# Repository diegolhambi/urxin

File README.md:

# Urxin

A keyboard made inspired by [Urchin](https://github.com/duckyb/urchin), [TOTEM](https://github.com/GEIGEIGEIST/TOTEM) and [Ergonaut One](https://github.com/ergonautkb/one).

## Firmware

A ZMK Module containing the shield can be found in [zmk-keyboard-urxin](https://github.com/diegolhambi/zmk-keyboard-urxin) and an example of implementation can be seen in [zmk-config-urxin](https://github.com/diegolhambi/zmk-config-urxin).

## BOM
List of parts for both sides.

| Name                          | Qty |
|-------------------------------|:---:|
| Kailh PG1350 Hot Swap Sockets |  34 |
| SOD-123 Diodes                |  34 |
| Seeeduino XIAO nRF52840       |  2  |
| Li-Po 601230 battery          |  2  |
| MSK-12C02 SPDT Switch         |  2  |

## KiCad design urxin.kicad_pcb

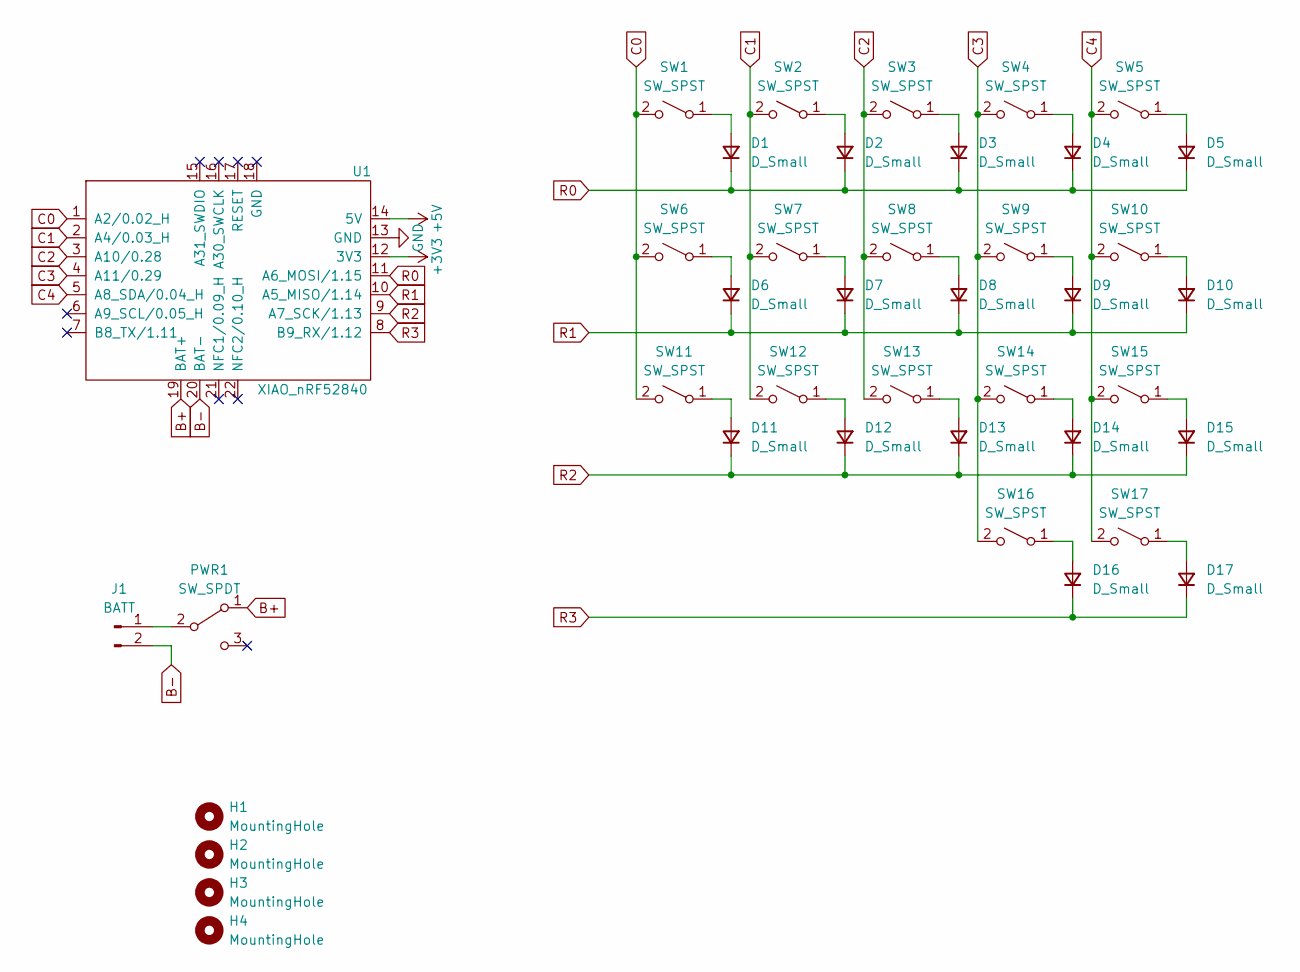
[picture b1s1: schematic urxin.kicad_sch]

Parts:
D1, D2, D3, D4, D5, D6, D7, D8, D9, D10, D11, D12, D13, D14, D15, D16, D17: D_Small; Diode_TH_SMD_DUAL
H1, H2, H3, H4: MountingHole; Hole_4.2mm
J1: BATT; Battery
PWR1: SW_SPDT; MSK-12C02_DUAL
SW1, SW2, SW3, SW4, SW5, SW6, SW7, SW8, SW9, SW10, SW11, SW12, SW13, SW14, SW15, SW16, SW17: SW_SPST; Kailh_socket_PG1350_1.00u_optional_millmax_reversible
U1: XIAO_nRF52840; XIAO_nRF52840_DUAL

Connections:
+3V3: U1.12 (3V3)
+5V: U1.14 (5V)
B+: PWR1.1 (A), U1.19 (BAT+)
B-: J1.2, U1.20 (BAT-)
C0: SW1.2 (B), SW6.2 (B), SW11.2 (B), U1.1 (A2/0.02_H)
C1: SW2.2 (B), SW7.2 (B), SW12.2 (B), U1.2 (A4/0.03_H)
C2: SW3.2 (B), SW8.2 (B), SW13.2 (B), U1.3 (A10/0.28)
C3: SW4.2 (B), SW9.2 (B), SW14.2 (B), SW16.2 (B), U1.4 (A11/0.29)
C4: SW5.2 (B), SW10.2 (B), SW15.2 (B), SW17.2 (B), U1.5 (A8_SDA/0.04_H)
GND: U1.13 (GND)
unnamed: D1.2 (A), SW1.1 (A)
unnamed: D2.2 (A), SW2.1 (A)
unnamed: D3.2 (A), SW3.1 (A)
unnamed: D4.2 (A), SW4.1 (A)
unnamed: D5.2 (A), SW5.1 (A)
unnamed: D6.2 (A), SW6.1 (A)
unnamed: D7.2 (A), SW7.1 (A)
unnamed: D8.2 (A), SW8.1 (A)
unnamed: D9.2 (A), SW9.1 (A)
unnamed: D10.2 (A), SW10.1 (A)
unnamed: D11.2 (A), SW11.1 (A)
unnamed: D12.2 (A), SW12.1 (A)
unnamed: D13.2 (A), SW13.1 (A)
unnamed: D14.2 (A), SW14.1 (A)
unnamed: D15.2 (A), SW15.1 (A)
unnamed: D16.2 (A), SW16.1 (A)
unnamed: D17.2 (A), SW17.1 (A)
unnamed: J1.1, PWR1.2 (B)
R0: D1.1 (K), D2.1 (K), D3.1 (K), D4.1 (K), D5.1 (K), U1.11 (A6_MOSI/1.15)
R1: D6.1 (K), D7.1 (K), D8.1 (K), D9.1 (K), D10.1 (K), U1.10 (A5_MISO/1.14)
R2: D11.1 (K), D12.1 (K), D13.1 (K), D14.1 (K), D15.1 (K), U1.9 (A7_SCK/1.13)
R3: D16.1 (K), D17.1 (K), U1.8 (B9_RX/1.12)

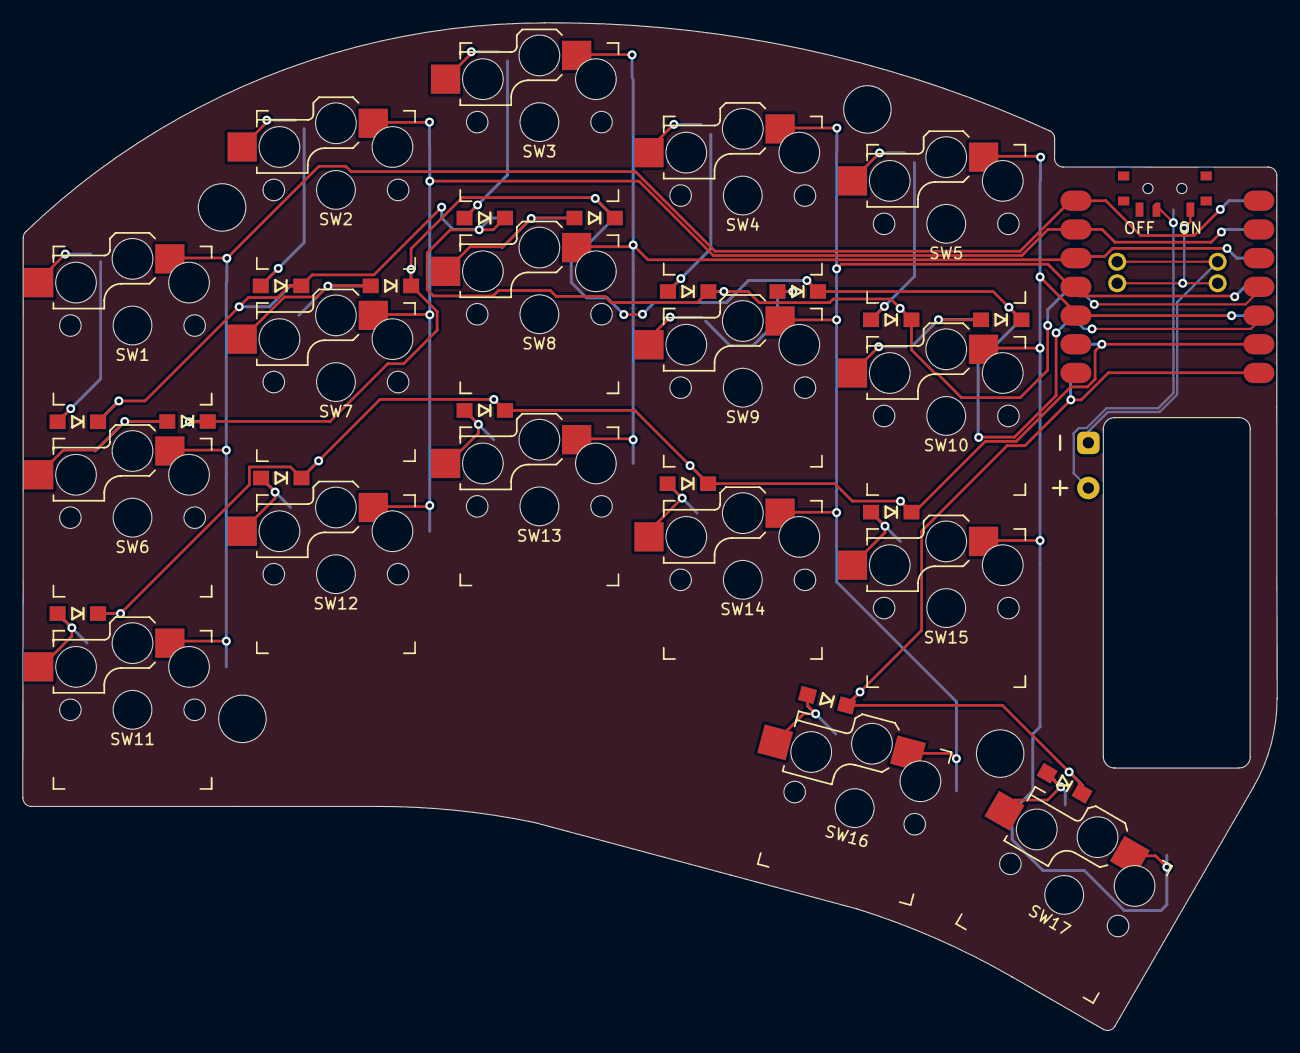
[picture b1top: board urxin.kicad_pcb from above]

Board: 2 copper layers, 110.9 x 89.1 mm, 41 parts (1 on the bottom side), 29 nets.

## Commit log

2024-10-14 feat: initial commit
2024-10-14 feat: add kicad files
2024-10-14 feat: add case files
2024-10-14 chore: update readme
2024-10-14 chore: fix links
2024-10-14 feat: add readme for the case
